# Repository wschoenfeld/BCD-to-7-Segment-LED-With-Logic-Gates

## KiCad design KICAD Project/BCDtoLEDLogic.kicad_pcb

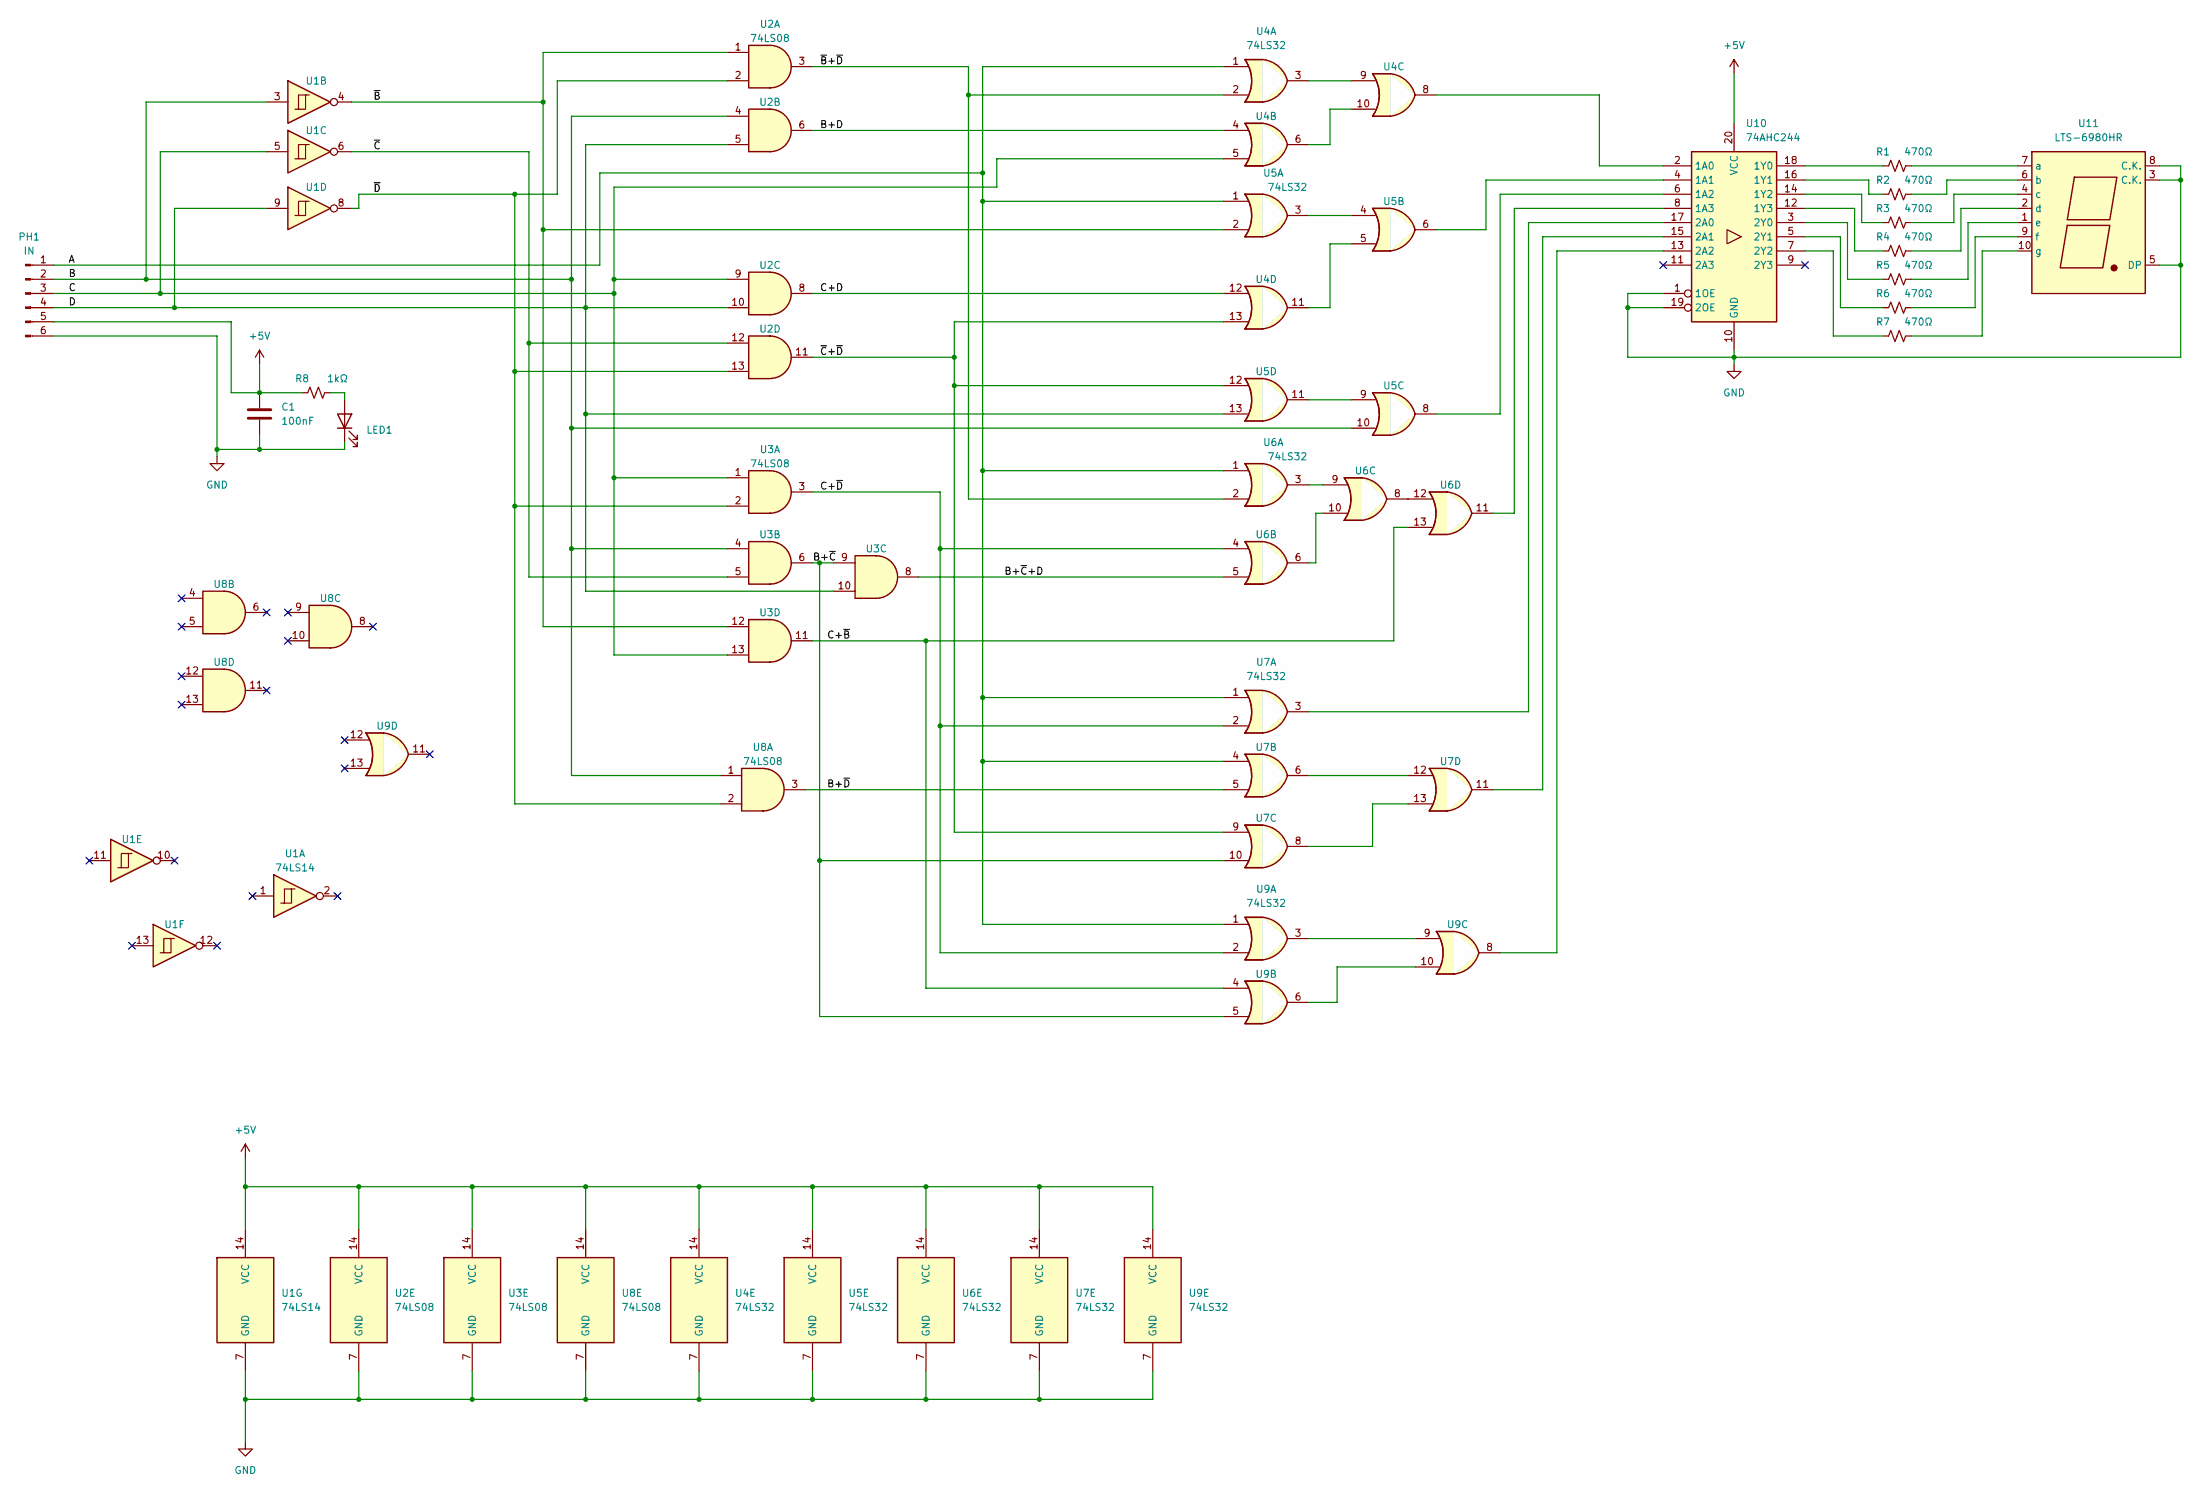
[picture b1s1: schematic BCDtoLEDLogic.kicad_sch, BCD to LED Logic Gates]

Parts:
C1: 100nF; C_Disc_D4.3mm_W1.9mm_P5.00mm
LED1: LED; LED_D3.0mm
PH1: IN; PinHeader_1x06_P2.54mm_Vertical
R1, R2, R3, R4, R5, R6, R7: 470Ω; R_Axial_DIN0207_L6.3mm_D2.5mm_P7.62mm_Horizontal
R8: 1kΩ; R_Axial_DIN0207_L6.3mm_D2.5mm_P7.62mm_Horizontal
U1: 74LS14; DIP-14_W7.62mm_Socket
U2, U3, U8: 74LS08; DIP-14_W7.62mm_Socket
U4, U5, U6, U7, U9: 74LS32; DIP-14_W7.62mm_Socket
U10: 74AHC244; DIP-20_W7.62mm_Socket
U11: LTS-6980HR; 7SegmentLED_LTS6760_LTS6780

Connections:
+5V: C1.1, PH1.5, R8.1, U1.14 (VCC), U2.14 (VCC), U3.14 (VCC), U4.14 (VCC), U5.14 (VCC), U6.14 (VCC), U7.14 (VCC), U8.14 (VCC), U9.14 (VCC), U10.20 (VCC)
/A: PH1.1, U4.1, U5.1, U6.1, U7.1, U7.4, U9.1
/B: PH1.2, U1.3, U2.4, U3.4, U5.10, U8.1
/B+D: U2.6, U4.4
/B+~C: U3.6, U3.9, U7.10, U9.5
/B+~C+D: U3.8, U6.5
/B+~D: U7.5, U8.3
/C: PH1.3, U1.5, U2.9, U3.1, U3.13, U4.5
/C+D: U2.8, U4.12
/C+~B: U3.11, U6.13, U9.4
/C+~D: U3.3, U6.4, U7.2, U9.2
/D: PH1.4, U1.9, U2.5, U2.10, U3.10, U5.13
/~B: U1.4, U2.1, U3.12, U5.2
/~B+~D: U2.3, U4.2, U6.2
/~C: U1.6, U2.12, U3.5
/~C+~D: U2.11, U4.13, U5.12, U7.9
/~D: U1.8, U2.2, U2.13, U3.2, U8.2
GND: C1.2, LED1.1 (K), PH1.6, U1.7 (GND), U2.7 (GND), U3.7 (GND), U4.7 (GND), U5.7 (GND), U6.7 (GND), U7.7 (GND), U8.7 (GND), U9.7 (GND), U10.1 (1OE), U10.10 (GND), U10.19 (2OE), U11.3 (C.K.), U11.5 (DP), U11.8 (C.K.)
unnamed: LED1.2 (A), R8.2
unnamed: R1.1, U10.18 (1Y0)
unnamed: R1.2, U11.7 (a)
unnamed: R2.1, U10.16 (1Y1)
unnamed: R2.2, U11.6 (b)
unnamed: R3.1, U10.14 (1Y2)
unnamed: R3.2, U11.4 (c)
unnamed: R4.1, U10.12 (1Y3)
unnamed: R4.2, U11.2 (d)
unnamed: R5.1, U10.3 (2Y0)
unnamed: R5.2, U11.1 (e)
unnamed: R6.1, U10.5 (2Y1)
unnamed: R6.2, U11.9 (f)
unnamed: R7.1, U10.7 (2Y2)
unnamed: R7.2, U11.10 (g)
unnamed: U4.3, U4.9
unnamed: U4.6, U4.10
unnamed: U4.11, U5.5
unnamed: U5.3, U5.4
unnamed: U5.9, U5.11
unnamed: U6.3, U6.9
unnamed: U6.6, U6.10
unnamed: U6.8, U6.12
unnamed: U7.6, U7.12
unnamed: U7.8, U7.13
unnamed: U9.3, U9.9
unnamed: U9.6, U9.10
unnamed: U4.8, U10.2 (1A0)
unnamed: U5.6, U10.4 (1A1)
unnamed: U5.8, U10.6 (1A2)
unnamed: U6.11, U10.8 (1A3)
unnamed: U9.8, U10.13 (2A2)
unnamed: U7.11, U10.15 (2A1)
unnamed: U7.3, U10.17 (2A0)

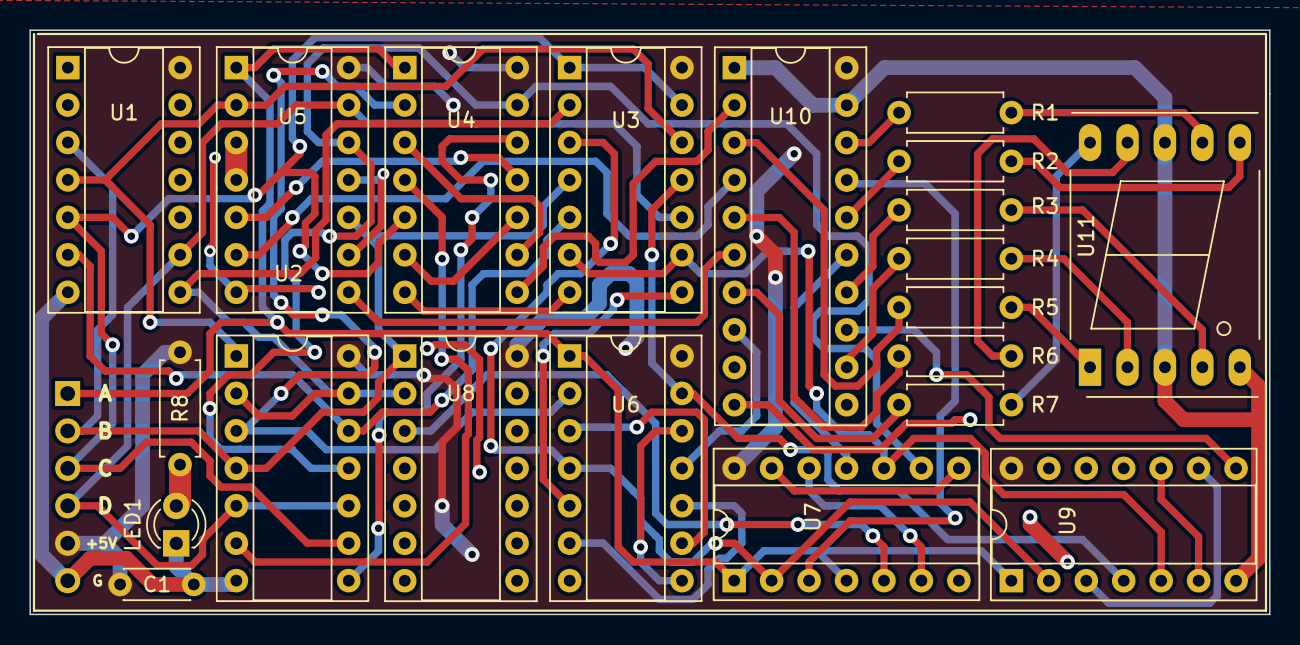
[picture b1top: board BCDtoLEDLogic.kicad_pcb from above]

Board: 2 copper layers, 84.1 x 39.6 mm, 22 parts (1 on the bottom side), 52 nets.
